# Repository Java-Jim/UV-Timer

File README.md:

# UV-Timer
simple Timer-Addon for my UV-exposure unit

https://hackaday.io/project/6087-uv-timer

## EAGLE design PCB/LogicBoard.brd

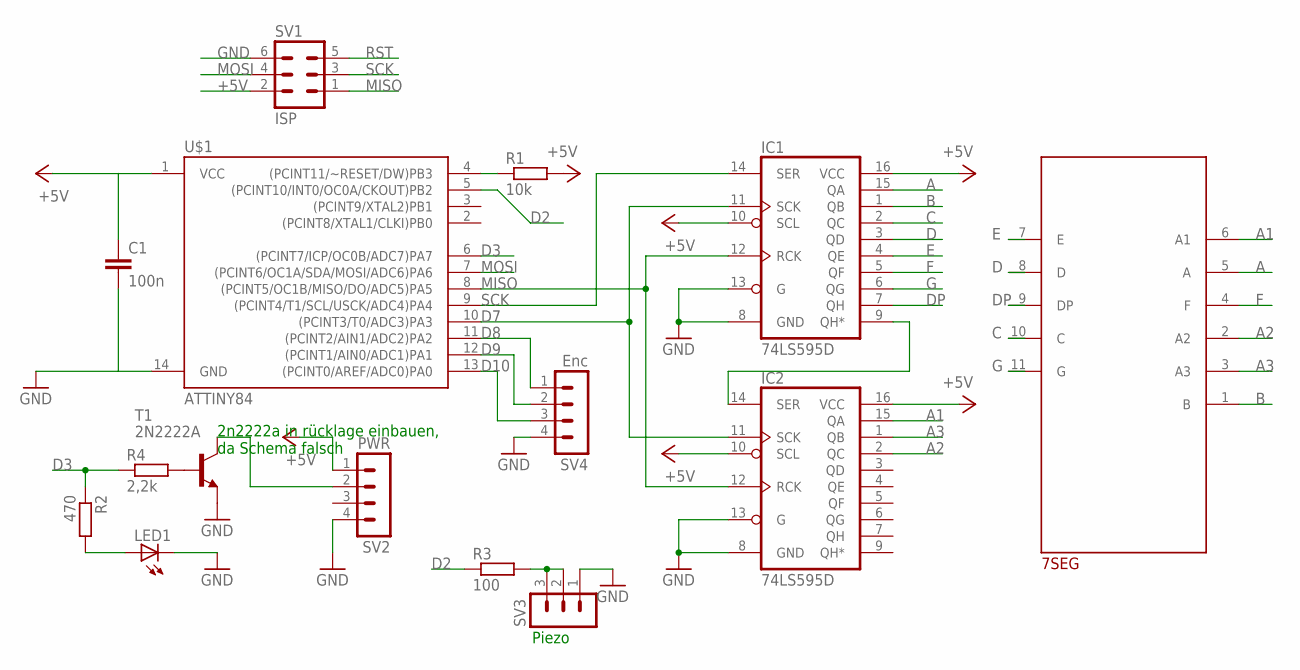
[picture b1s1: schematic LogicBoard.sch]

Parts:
7SEG: TOT4301TOT-4301FG1; TOT4301
C1: 100n; C0805
IC1, IC2: 74LS595D; SO16
LED1: LED5MM
R1: 10k; M0805
R2: 470; M0805
R3: 100; M0805
R4: 2,2k; M0805
SV1: ISP; MA03-2
SV2: PWR; MA04-1
SV3: MA03-1
SV4: Enc; MA04-1
T1: 2N2222A; SOT23-EBC
U$1: ATTINY84; SO14

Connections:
+5V: C1.1, IC1.10 (SCL), IC1.16 (VCC), IC2.10 (SCL), IC2.16 (VCC), R1.2, SV1.2, SV2.1, U$1.1 (VCC)
A: 7SEG.5 (A), IC1.15 (QA)
A1: 7SEG.6 (A1), IC2.15 (QA)
A2: 7SEG.2 (A2), IC2.2 (QC)
A3: 7SEG.3 (A3), IC2.1 (QB)
B: 7SEG.1 (B), IC1.1 (QB)
C: 7SEG.10 (C), IC1.2 (QC)
D: 7SEG.8 (D), IC1.3 (QD)
D2: R3.1, U$1.5 ((PCINT10/INT0/OC0A/CKOUT)PB2)
D3: R2.1, R4.1, U$1.6 ((PCINT7/ICP/OC0B/ADC7)PA7)
D7: IC1.11 (SCK), IC2.11 (SCK), U$1.10 ((PCINT3/T0/ADC3)PA3)
D8: SV4.1, U$1.11 ((PCINT2/AIN1/ADC2)PA2)
D9: SV4.2, U$1.12 ((PCINT1/AIN0/ADC1)PA1)
D10: SV4.3, U$1.13 ((PCINT0/AREF/ADC0)PA0)
DP: 7SEG.9 (DP), IC1.7 (QH)
E: 7SEG.7 (E), IC1.4 (QE)
F: 7SEG.4 (F), IC1.5 (QF)
G: 7SEG.11 (G), IC1.6 (QG)
GND: C1.2, IC1.8 (GND), IC1.13 (G), IC2.8 (GND), IC2.13 (G), LED1.K (C), SV1.6, SV2.4, SV3.1, SV4.4, T1.E, U$1.14 (GND)
MISO: IC1.12 (RCK), IC2.12 (RCK), SV1.1, U$1.8 ((PCINT5/OC1B/MISO/DO/ADC5)PA5)
MOSI: SV1.4, U$1.7 ((PCINT6/OC1A/SDA/MOSI/ADC6)PA6)
unnamed: LED1.A, R2.2
unnamed: R3.2, SV3.2, SV3.3
unnamed: R4.2, T1.B
unnamed: SV2.2, T1.C
OE: IC1.9 (QH*), IC2.14 (SER)
RST: R1.1, SV1.5, U$1.4 ((PCINT11/~RESET/DW)PB3)
SCK: IC1.14 (SER), SV1.3, U$1.9 ((PCINT4/T1/SCL/USCK/ADC4)PA4)

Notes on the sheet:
Piezo
2n2222a in rücklage einbauen, da Schema falsch

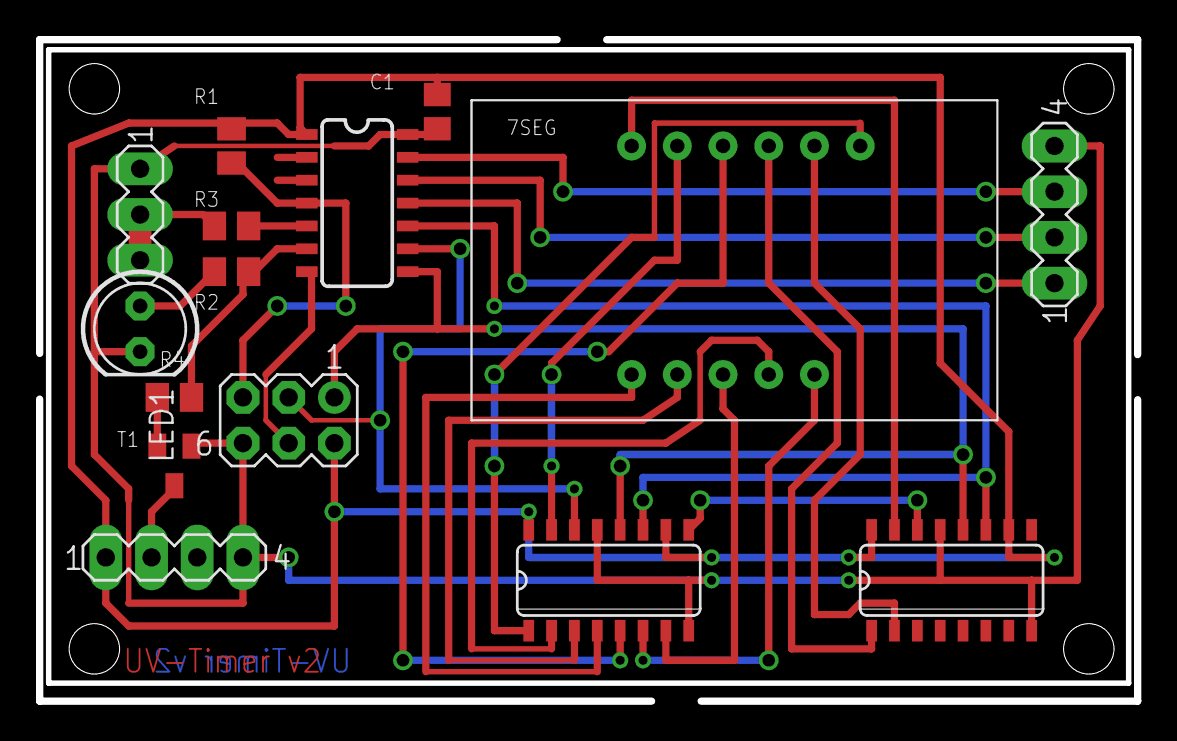
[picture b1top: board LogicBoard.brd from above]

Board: 2 copper layers, 61.0 x 36.8 mm, 15 parts (0 on the bottom side), 28 nets.

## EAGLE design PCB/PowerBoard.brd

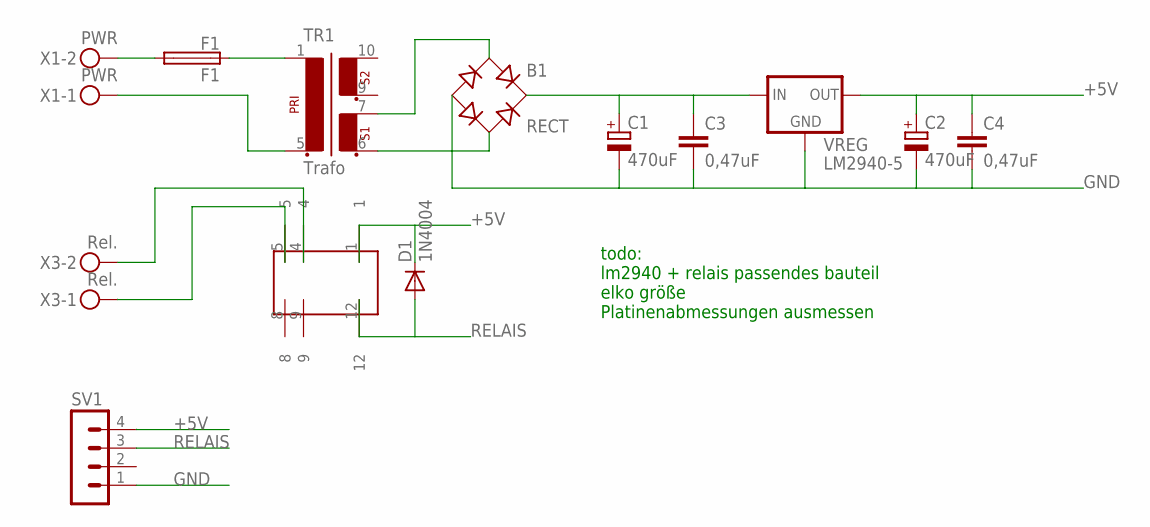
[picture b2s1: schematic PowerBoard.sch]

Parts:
B1: RECT; 1KAB
C1, C2: 470uF; E5-6
C3, C4: 0,47uF; C025-030X050
D1: 1N4004; DO41-10
F1: F1; FUSE_HOLDER_5X20MM
SV1: MA04-1
TR1: Trafo; EI30-2
U$1: V23079-A
VREG: LM2940-5; 78MXXS
X1: PWR; MKDSN1,5/2-5,08
X3: Rel.; MKDSN1,5/2-5,08

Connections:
+5V: C2.+, C4.1, D1.C, SV1.4, U$1.1, VREG.OUT
GND: B1.-, C1.-, C2.-, C3.2, C4.2, SV1.1, VREG.GND
unnamed: B1.AC2, TR1.6 (3)
unnamed: B1.AC1, TR1.7 (4)
unnamed: U$1.4, X3.2
unnamed: B1.+, C1.+, C3.1, VREG.IN
unnamed: U$1.5, X3.1
unnamed: TR1.5 (2), X1.1
unnamed: F1.2, X1.2
RELAIS: D1.A, SV1.3, U$1.12
TRAFO: F1.1, TR1.1

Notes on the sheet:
todo: lm2940 + relais passendes bauteil elko größe Platinenabmessungen ausmessen

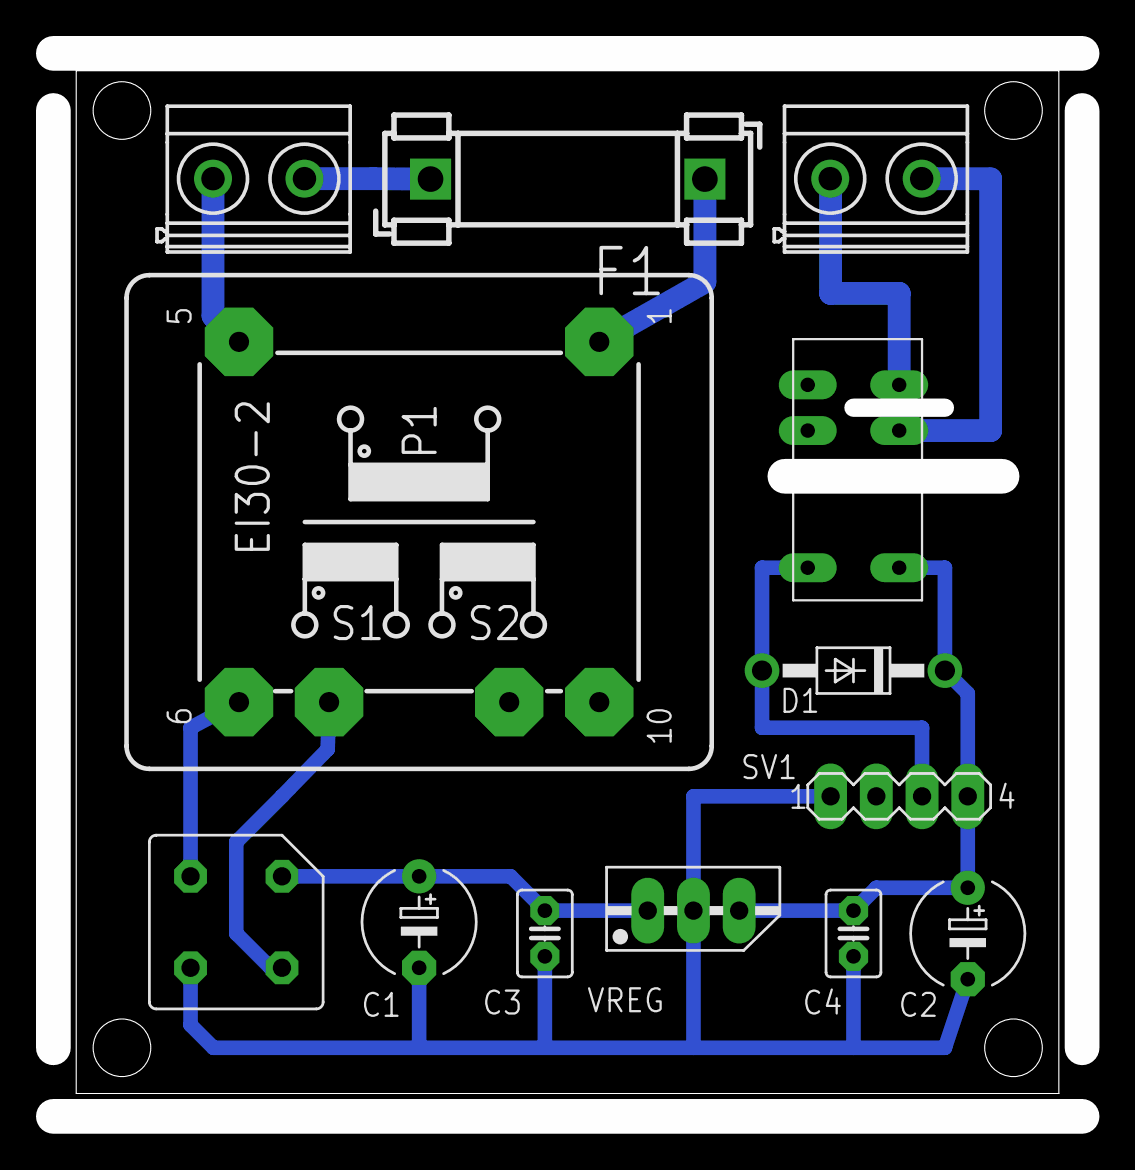
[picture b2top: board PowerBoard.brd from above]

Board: 2 copper layers, 57.2 x 59.1 mm, 13 parts (0 on the bottom side), 11 nets.

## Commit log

2015-06-02 EAGLE LogicBoard Schematic
2015-06-02 EAGLE PowerBoard Schematic
2015-06-02 CNC File for LaserCutter
2015-06-02 EAGLE PowerBoard Board
2015-06-02 EAGLE LogicBoard Board

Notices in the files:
parts and their libraries:
SparkFun-DigitalIC: Licensing: Creative Commons ShareAlike 4.0 International - https://creativecommons.org/licenses/by-sa/4.0
